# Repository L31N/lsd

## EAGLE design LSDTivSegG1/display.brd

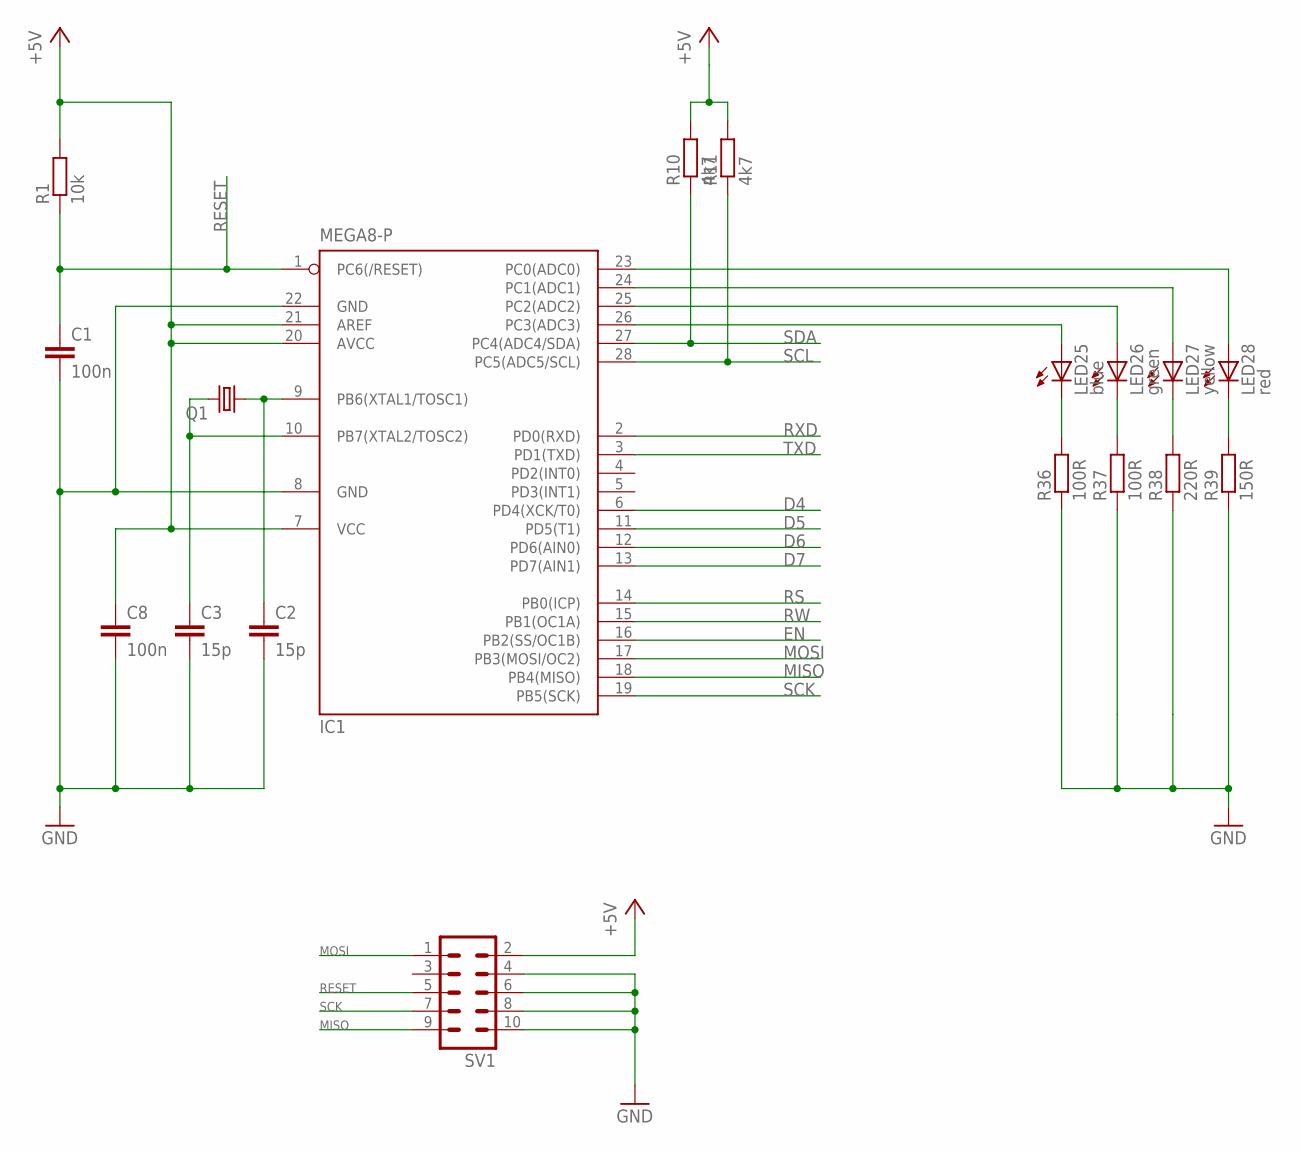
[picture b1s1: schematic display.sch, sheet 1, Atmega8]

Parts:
C1, C8: 100n; C025-025X050
C2, C3: 15p; C025-025X050
IC1: MEGA8-P; DIL28-3
LED25: blue; LED3MM
LED26: green; LED3MM
LED27: yellow; LED3MM
LED28: red; LED3MM
Q1: CRYSTALHC49U-V; HC49U-V
R1: 10k; 0207/10
R10, R11: 4k7; 0207/10
R36, R37: 100R; 0207/10
R38: 220R; 0207/10
R39: 150R; 0207/10
SV1: ML10

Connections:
+5V: C8.1, IC1.7 (VCC), IC1.20 (AVCC), IC1.21 (AREF), R1.2, R10.2, R11.2, SV1.2; also elsewhere on the board
D4: IC1.6 (PD4(XCK/T0)); also elsewhere on the board
D5: IC1.11 (PD5(T1)); also elsewhere on the board
D6: IC1.12 (PD6(AIN0)); also elsewhere on the board
D7: IC1.13 (PD7(AIN1)); also elsewhere on the board
EN: IC1.16 (PB2(SS/OC1B)); also elsewhere on the board
GND: C1.2, C2.2, C3.2, C8.2, IC1.8 (GND), IC1.22 (GND), R36.1, R37.1, R38.1, R39.1, SV1.4, SV1.6, SV1.8, SV1.10; also elsewhere on the board
MISO: IC1.18 (PB4(MISO)), SV1.9
MOSI: IC1.17 (PB3(MOSI/OC2)), SV1.1
unnamed: C2.1, IC1.9 (PB6(XTAL1/TOSC1)), Q1.1
unnamed: C3.1, IC1.10 (PB7(XTAL2/TOSC2)), Q1.2
unnamed: IC1.23 (PC0(ADC0)), LED28.A
unnamed: IC1.24 (PC1(ADC1)), LED27.A
unnamed: IC1.25 (PC2(ADC2)), LED26.A
unnamed: IC1.26 (PC3(ADC3)), LED25.A
unnamed: LED28.K (C), R39.2
unnamed: LED27.K (C), R38.2
unnamed: LED26.K (C), R37.2
unnamed: LED25.K (C), R36.2
RESET: C1.1, IC1.1 (PC6(/RESET)), R1.1, SV1.5
RS: IC1.14 (PB0(ICP)); also elsewhere on the board
RW: IC1.15 (PB1(OC1A)); also elsewhere on the board
RXD: IC1.2 (PD0(RXD)); also elsewhere on the board
SCK: IC1.19 (PB5(SCK)), SV1.7
SCL: IC1.28 (PC5(ADC5/SCL)), R11.1; also elsewhere on the board
SDA: IC1.27 (PC4(ADC4/SDA)), R10.1; also elsewhere on the board
TXD: IC1.3 (PD1(TXD)); also elsewhere on the board

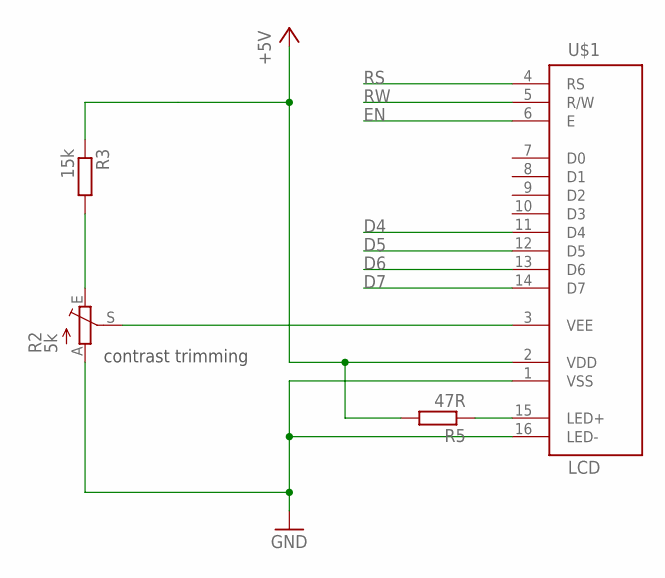
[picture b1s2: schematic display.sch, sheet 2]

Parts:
R2: 5k; PT-10
R3: 15k; 0207/10
R5: 47R; 0207/10
U$1: LCD

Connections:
+5V: R3.1, R5.2, U$1.2 (VDD); also elsewhere on the board
D4: U$1.11 (D4); also elsewhere on the board
D5: U$1.12 (D5); also elsewhere on the board
D6: U$1.13 (D6); also elsewhere on the board
D7: U$1.14 (D7); also elsewhere on the board
EN: U$1.6 (E); also elsewhere on the board
GND: R2.A, U$1.1 (VSS), U$1.16 (LED-); also elsewhere on the board
unnamed: R2.E, R3.2
unnamed: R2.S, U$1.3 (VEE)
unnamed: R5.1, U$1.15 (LED+)
RS: U$1.4 (RS); also elsewhere on the board
RW: U$1.5 (R/W); also elsewhere on the board

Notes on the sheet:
contrast trimming

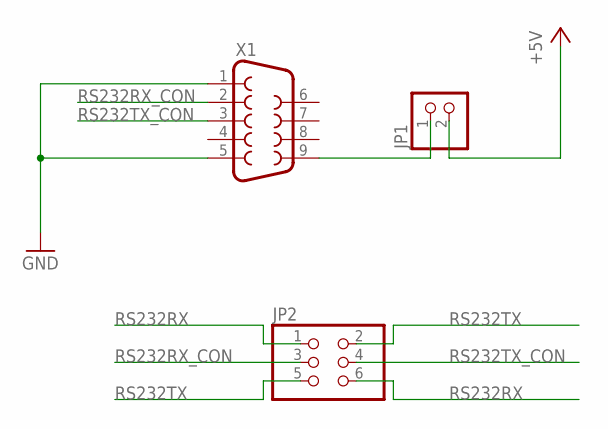
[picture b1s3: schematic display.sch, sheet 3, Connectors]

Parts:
JP1: PINHD-1X2; 1X02
JP2: PINHD-2X3; 2X03
X1: F09HP

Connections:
+5V: JP1.2; also elsewhere on the board
GND: X1.1, X1.5; also elsewhere on the board
unnamed: JP1.1, X1.9
RS232RX: JP2.1, JP2.6; also elsewhere on the board
RS232RX_CON: JP2.3, X1.2
RS232TX: JP2.2, JP2.5; also elsewhere on the board
RS232TX_CON: JP2.4, X1.3

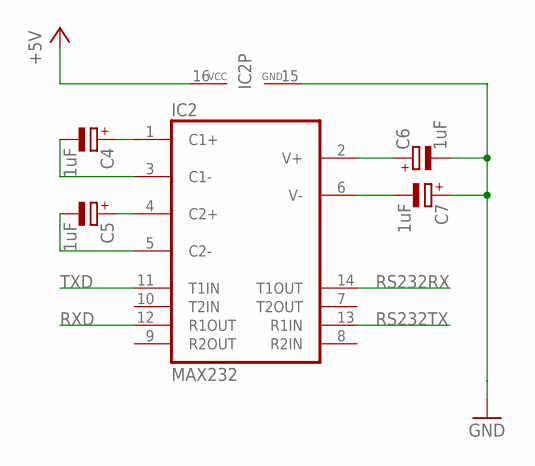
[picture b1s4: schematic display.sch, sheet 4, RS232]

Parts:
C4, C5, C6, C7: 1uF; E2,5-5
IC2: MAX232; DIL16

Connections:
+5V: IC2.16 (VCC); also elsewhere on the board
GND: C6.-, C7.+, IC2.15 (GND); also elsewhere on the board
unnamed: C4.+, IC2.1 (C1+)
unnamed: C5.+, IC2.4 (C2+)
unnamed: C5.-, IC2.5 (C2-)
unnamed: C4.-, IC2.3 (C1-)
unnamed: C6.+, IC2.2 (V+)
unnamed: C7.-, IC2.6 (V-)
RS232RX: IC2.14 (T1OUT); also elsewhere on the board
RS232TX: IC2.13 (R1IN); also elsewhere on the board
RXD: IC2.12 (R1OUT); also elsewhere on the board
TXD: IC2.11 (T1IN); also elsewhere on the board

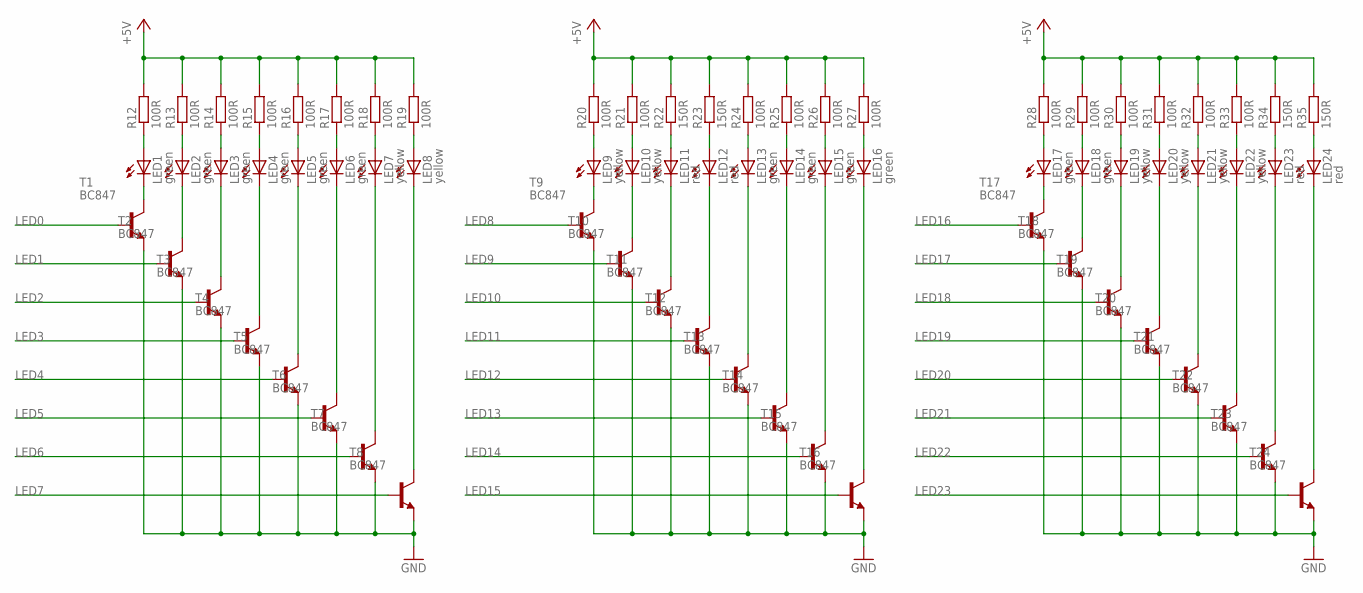
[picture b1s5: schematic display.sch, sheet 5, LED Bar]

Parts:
LED1, LED2, LED3, LED4, LED5, LED6, LED13, LED14, LED15, LED16, LED17, LED18: green; LED5MM
LED7, LED8, LED9, LED10, LED19, LED20, LED21, LED22: yellow; LED5MM
LED11, LED12, LED23, LED24: red; LED5MM
R12, R13, R14, R15, R16, R17, R18, R19, R20, R21, R24, R25, R26, R27, R28, R29, R30, R31, R32, R33: 100R; 0207/10
R22, R23, R34, R35: 150R; 0207/10
T1, T2, T3, T4, T5, T6, T7, T8, T9, T10, T11, T12, T13, T14, T15, T16, T17, T18, T19, T20, T21, T22, T23, T24: BC847; SOT23

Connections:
+5V: R12.2, R13.2, R14.2, R15.2, R16.2, R17.2, R18.2, R19.2, R20.2, R21.2, R22.2, R23.2, R24.2, R25.2, R26.2, R27.2, R28.2, R29.2, R30.2, R31.2, R32.2, R33.2, R34.2, R35.2; also elsewhere on the board
GND: T1.2 (E), T2.2 (E), T3.2 (E), T4.2 (E), T5.2 (E), T6.2 (E), T7.2 (E), T8.2 (E), T9.2 (E), T10.2 (E), T11.2 (E), T12.2 (E), T13.2 (E), T14.2 (E), T15.2 (E), T16.2 (E), T17.2 (E), T18.2 (E), T19.2 (E), T20.2 (E), T21.2 (E), T22.2 (E), T23.2 (E), T24.2 (E); also elsewhere on the board
LED0: T1.1 (B); also elsewhere on the board
LED1: T2.1 (B); also elsewhere on the board
LED2: T3.1 (B); also elsewhere on the board
LED3: T4.1 (B); also elsewhere on the board
LED4: T5.1 (B); also elsewhere on the board
LED5: T6.1 (B); also elsewhere on the board
LED6: T7.1 (B); also elsewhere on the board
LED7: T8.1 (B); also elsewhere on the board
LED8: T9.1 (B); also elsewhere on the board
LED9: T10.1 (B); also elsewhere on the board
LED10: T11.1 (B); also elsewhere on the board
LED11: T12.1 (B); also elsewhere on the board
LED12: T13.1 (B); also elsewhere on the board
LED13: T14.1 (B); also elsewhere on the board
LED14: T15.1 (B); also elsewhere on the board
LED15: T16.1 (B); also elsewhere on the board
LED16: T17.1 (B); also elsewhere on the board
LED17: T18.1 (B); also elsewhere on the board
LED18: T19.1 (B); also elsewhere on the board
LED19: T20.1 (B); also elsewhere on the board
LED20: T21.1 (B); also elsewhere on the board
LED21: T22.1 (B); also elsewhere on the board
LED22: T23.1 (B); also elsewhere on the board
LED23: T24.1 (B); also elsewhere on the board
unnamed: LED1.A, R12.1
unnamed: LED2.A, R13.1
unnamed: LED3.A, R14.1
unnamed: LED4.A, R15.1
unnamed: LED5.A, R16.1
unnamed: LED6.A, R17.1
unnamed: LED7.A, R18.1
unnamed: LED8.A, R19.1
unnamed: LED9.A, R20.1
unnamed: LED10.A, R21.1
unnamed: LED11.A, R22.1
unnamed: LED12.A, R23.1
unnamed: LED13.A, R24.1
unnamed: LED14.A, R25.1
unnamed: LED15.A, R26.1
unnamed: LED16.A, R27.1
unnamed: LED17.A, R28.1
unnamed: LED18.A, R29.1
unnamed: LED19.A, R30.1
unnamed: LED20.A, R31.1
unnamed: LED21.A, R32.1
unnamed: LED22.A, R33.1
unnamed: LED23.A, R34.1
unnamed: LED24.A, R35.1
unnamed: LED9.K (C), T9.3 (C)
unnamed: LED1.K (C), T1.3 (C)
unnamed: LED2.K (C), T2.3 (C)
unnamed: LED3.K (C), T3.3 (C)
unnamed: LED4.K (C), T4.3 (C)
unnamed: LED5.K (C), T5.3 (C)
unnamed: LED6.K (C), T6.3 (C)
unnamed: LED17.K (C), T17.3 (C)
unnamed: LED10.K (C), T10.3 (C)
unnamed: LED11.K (C), T11.3 (C)
unnamed: LED12.K (C), T12.3 (C)
unnamed: LED13.K (C), T13.3 (C)
unnamed: LED14.K (C), T14.3 (C)
unnamed: LED7.K (C), T7.3 (C)
unnamed: LED8.K (C), T8.3 (C)
unnamed: LED15.K (C), T15.3 (C)
unnamed: LED16.K (C), T16.3 (C)
unnamed: LED18.K (C), T18.3 (C)
unnamed: LED19.K (C), T19.3 (C)
unnamed: LED20.K (C), T20.3 (C)
unnamed: LED21.K (C), T21.3 (C)
unnamed: LED22.K (C), T22.3 (C)
unnamed: LED23.K (C), T23.3 (C)
unnamed: LED24.K (C), T24.3 (C)

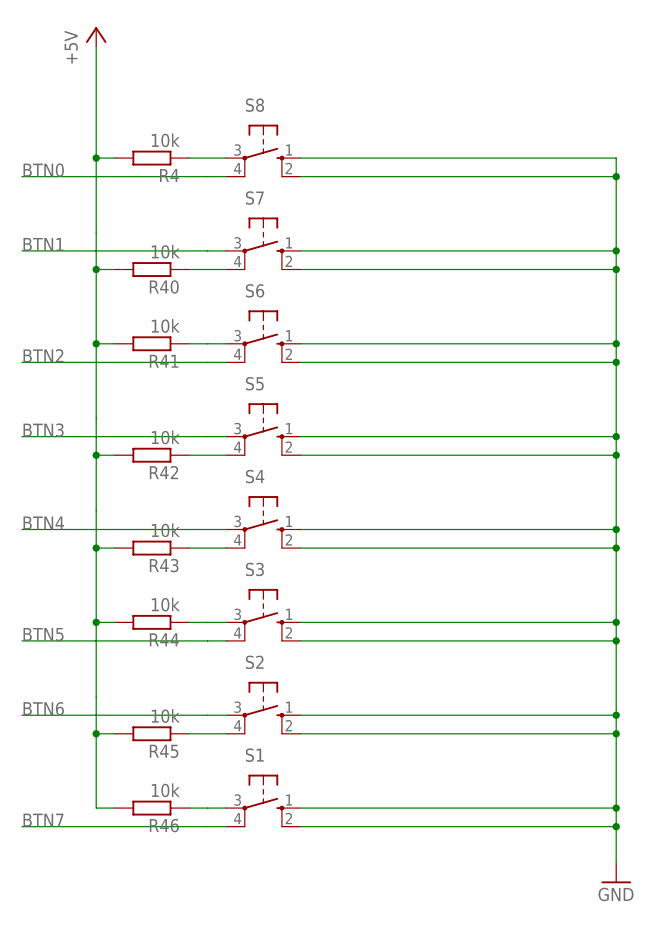
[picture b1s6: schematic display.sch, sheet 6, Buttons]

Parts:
R4, R40, R41, R42, R43, R44, R45, R46: 10k; R0805
S1, S2, S3, S4, S5, S6, S7, S8: 10-XX; B3F-10XX

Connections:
+5V: R4.2, R40.2, R41.2, R42.2, R43.2, R44.2, R45.2, R46.2; also elsewhere on the board
BTN0: S8.4 (P1); also elsewhere on the board
BTN1: S7.3; also elsewhere on the board
BTN2: S6.4 (P1); also elsewhere on the board
BTN3: S5.3; also elsewhere on the board
BTN4: S4.3; also elsewhere on the board
BTN5: S3.4 (P1); also elsewhere on the board
BTN6: S2.3; also elsewhere on the board
BTN7: S1.4 (P1); also elsewhere on the board
GND: S1.1 (S), S1.2 (S1), S2.1 (S), S2.2 (S1), S3.1 (S), S3.2 (S1), S4.1 (S), S4.2 (S1), S5.1 (S), S5.2 (S1), S6.1 (S), S6.2 (S1), S7.1 (S), S7.2 (S1), S8.1 (S), S8.2 (S1); also elsewhere on the board
unnamed: R4.1, S8.3
unnamed: R41.1, S6.3
unnamed: R45.1, S2.4 (P1)
unnamed: R43.1, S4.4 (P1)
unnamed: R44.1, S3.3
unnamed: R42.1, S5.4 (P1)
unnamed: R46.1, S1.3
unnamed: R40.1, S7.4 (P1)

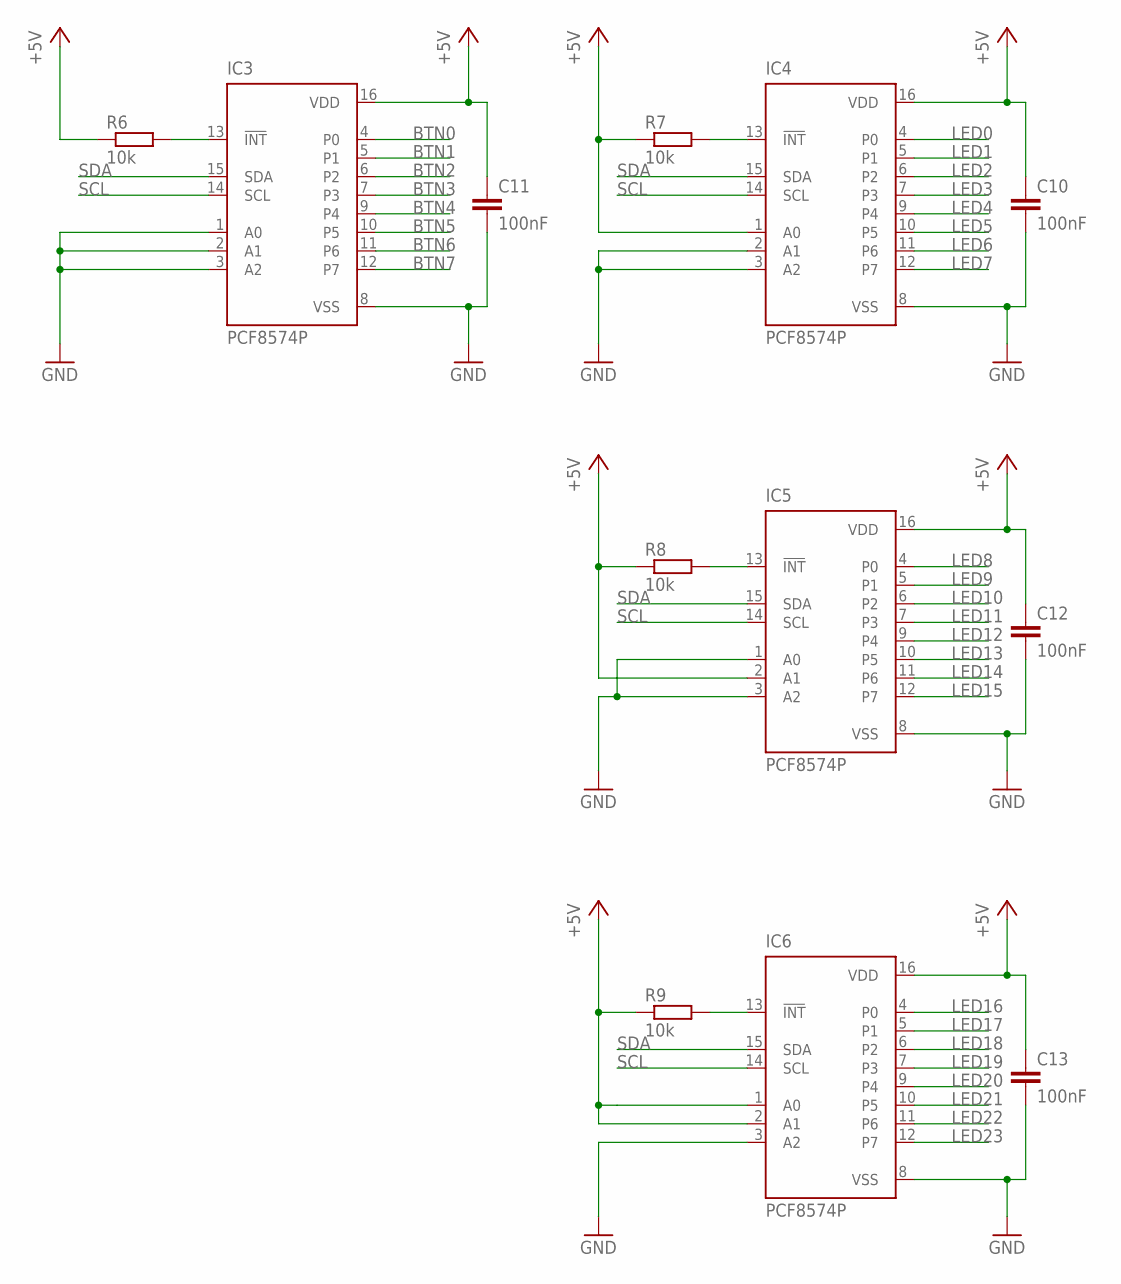
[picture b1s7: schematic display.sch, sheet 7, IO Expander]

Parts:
C10, C11, C12, C13: 100nF; C025-025X050
IC3, IC4, IC5, IC6: PCF8574P; DIL16
R6, R7, R8, R9: 10k; 0207/10

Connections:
+5V: C10.1, C11.1, C12.1, C13.1, IC3.16 (VDD), IC4.1 (A0), IC4.16 (VDD), IC5.2 (A1), IC5.16 (VDD), IC6.1 (A0), IC6.2 (A1), IC6.16 (VDD), R6.1, R7.1, R8.1, R9.1; also elsewhere on the board
BTN0: IC3.4 (P0); also elsewhere on the board
BTN1: IC3.5 (P1); also elsewhere on the board
BTN2: IC3.6 (P2); also elsewhere on the board
BTN3: IC3.7 (P3); also elsewhere on the board
BTN4: IC3.9 (P4); also elsewhere on the board
BTN5: IC3.10 (P5); also elsewhere on the board
BTN6: IC3.11 (P6); also elsewhere on the board
BTN7: IC3.12 (P7); also elsewhere on the board
GND: C10.2, C11.2, C12.2, C13.2, IC3.1 (A0), IC3.2 (A1), IC3.3 (A2), IC3.8 (VSS), IC4.2 (A1), IC4.3 (A2), IC4.8 (VSS), IC5.1 (A0), IC5.3 (A2), IC5.8 (VSS), IC6.3 (A2), IC6.8 (VSS); also elsewhere on the board
LED0: IC4.4 (P0); also elsewhere on the board
LED1: IC4.5 (P1); also elsewhere on the board
LED2: IC4.6 (P2); also elsewhere on the board
LED3: IC4.7 (P3); also elsewhere on the board
LED4: IC4.9 (P4); also elsewhere on the board
LED5: IC4.10 (P5); also elsewhere on the board
LED6: IC4.11 (P6); also elsewhere on the board
LED7: IC4.12 (P7); also elsewhere on the board
LED8: IC5.4 (P0); also elsewhere on the board
LED9: IC5.5 (P1); also elsewhere on the board
LED10: IC5.6 (P2); also elsewhere on the board
LED11: IC5.7 (P3); also elsewhere on the board
LED12: IC5.9 (P4); also elsewhere on the board
LED13: IC5.10 (P5); also elsewhere on the board
LED14: IC5.11 (P6); also elsewhere on the board
LED15: IC5.12 (P7); also elsewhere on the board
LED16: IC6.4 (P0); also elsewhere on the board
LED17: IC6.5 (P1); also elsewhere on the board
LED18: IC6.6 (P2); also elsewhere on the board
LED19: IC6.7 (P3); also elsewhere on the board
LED20: IC6.9 (P4); also elsewhere on the board
LED21: IC6.10 (P5); also elsewhere on the board
LED22: IC6.11 (P6); also elsewhere on the board
LED23: IC6.12 (P7); also elsewhere on the board
unnamed: IC3.13 (!INT), R6.2
unnamed: IC4.13 (!INT), R7.2
unnamed: IC5.13 (!INT), R8.2
unnamed: IC6.13 (!INT), R9.2
SCL: IC3.14 (SCL), IC4.14 (SCL), IC5.14 (SCL), IC6.14 (SCL); also elsewhere on the board
SDA: IC3.15 (SDA), IC4.15 (SDA), IC5.15 (SDA), IC6.15 (SDA); also elsewhere on the board

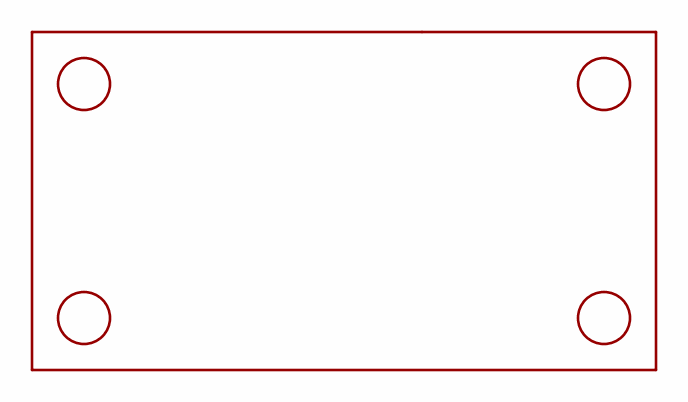
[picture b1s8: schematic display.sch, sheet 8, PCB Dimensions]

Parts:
U$2: DISPLAY_FRAME

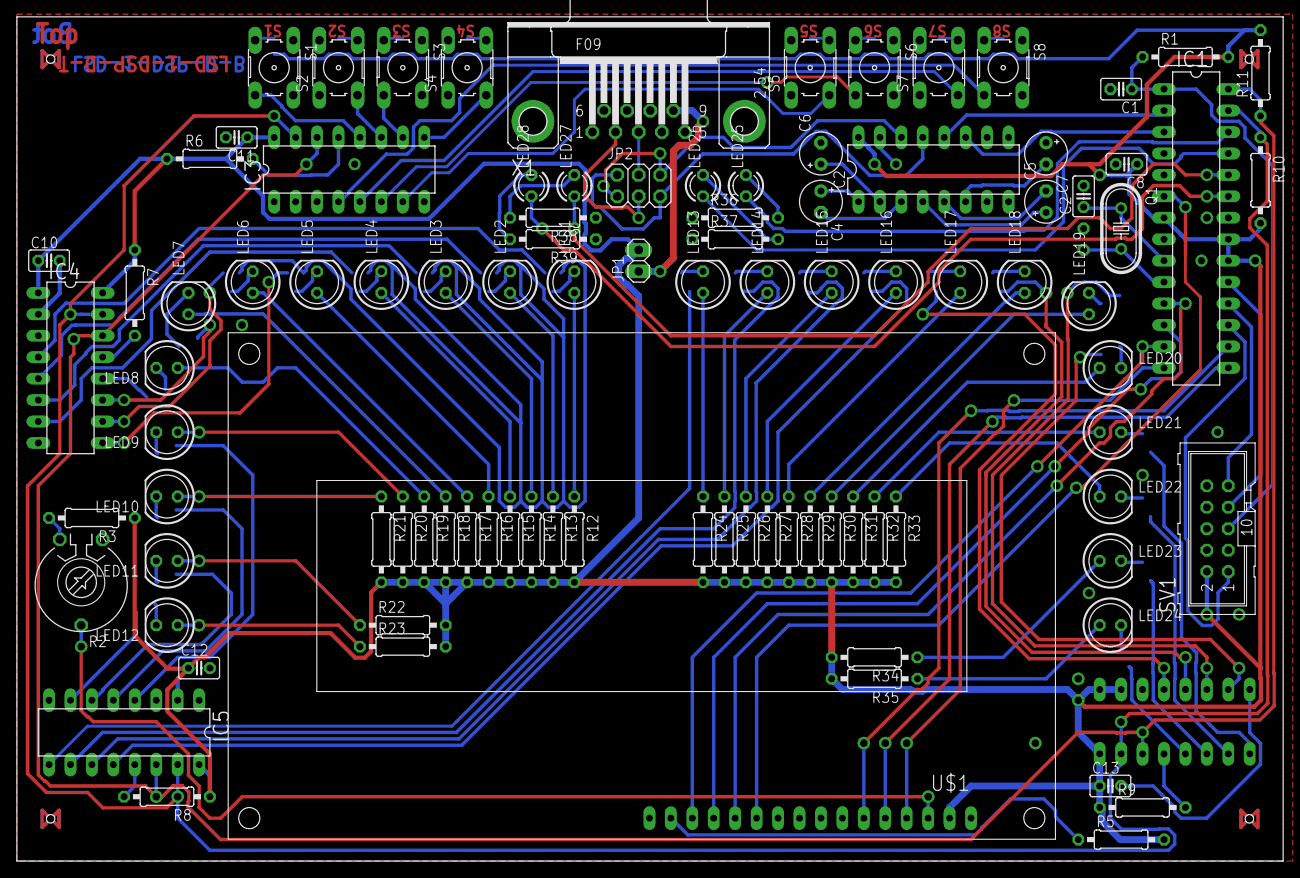
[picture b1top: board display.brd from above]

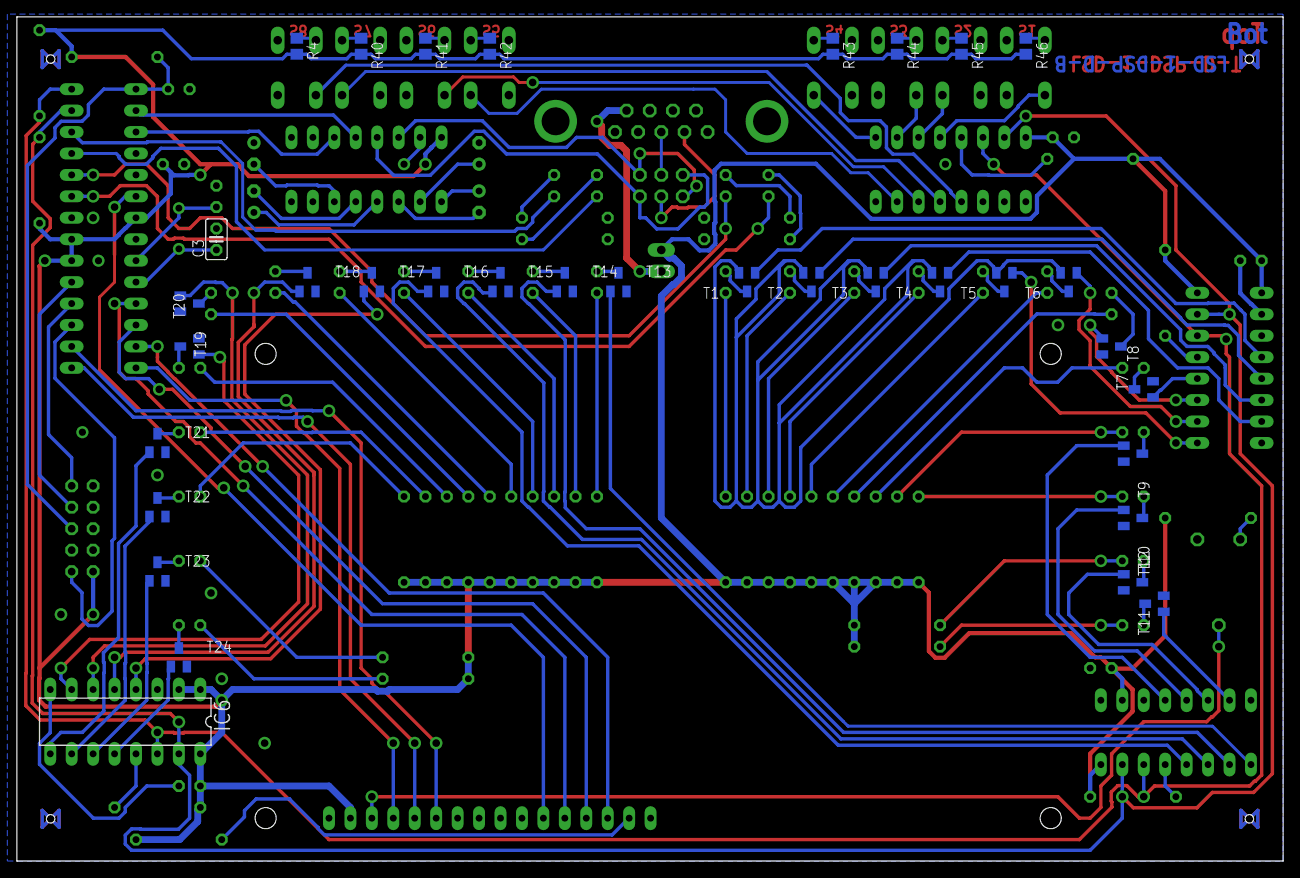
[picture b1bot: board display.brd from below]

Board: 2 copper layers, 150.0 x 100.0 mm, 131 parts (34 on the bottom side), 133 nets.

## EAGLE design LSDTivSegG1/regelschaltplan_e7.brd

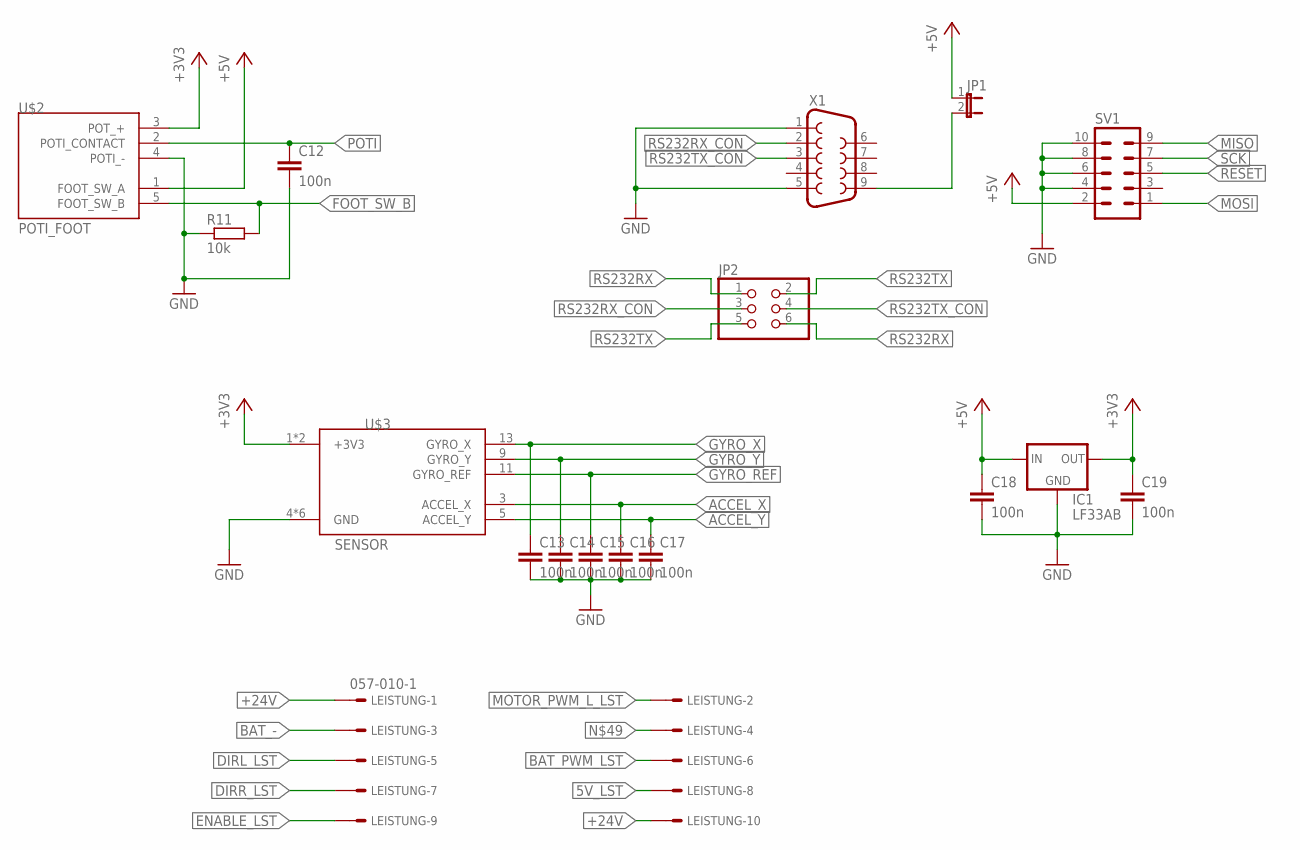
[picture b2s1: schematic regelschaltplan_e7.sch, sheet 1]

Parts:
C12, C13, C14, C15, C16, C17, C18, C19: 100n; C025-025X050
IC1: LF33AB; TO220
JP1: JP1E; JP1
JP2: PINHD-2X3; 2X03
LEISTUNG: 057-010-1
R11: 10k; 0207/7
SV1: MA05-2
U$2: POTI_FOOT; CON_6
U$3: SENSOR; CON_14
X1: F09HP

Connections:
5V_LST: LEISTUNG.8; also elsewhere on the board
+3V3: C19.1, IC1.3 (OUT), U$2.3 (POT_+), U$3.1 (+3V3), U$3.2 (+3V3); also elsewhere on the board
+24V: LEISTUNG.1, LEISTUNG.10; also elsewhere on the board
ACCEL_X: C16.1, U$3.3 (ACCEL_X); also elsewhere on the board
ACCEL_Y: C17.1, U$3.5 (ACCEL_Y); also elsewhere on the board
BAT_-: LEISTUNG.3; also elsewhere on the board
BAT_PWM_LST: LEISTUNG.6; also elsewhere on the board
DIRL_LST: LEISTUNG.5; also elsewhere on the board
DIRR_LST: LEISTUNG.7; also elsewhere on the board
ENABLE_LST: LEISTUNG.9; also elsewhere on the board
FOOT_SW_B: R11.2, U$2.5 (FOOT_SW_B); also elsewhere on the board
GND: C12.2, C13.2, C14.2, C15.2, C16.2, C17.2, C18.2, C19.2, IC1.2 (GND), R11.1, SV1.4, SV1.6, SV1.8, SV1.10, U$2.4 (POTI_-), U$3.4 (GND), U$3.6 (GND), U$3.8 (GND), U$3.10 (GND), U$3.12 (GND), U$3.14 (GND), X1.1, X1.5; also elsewhere on the board
GYRO_REF: C15.1, U$3.11 (GYRO_REF); also elsewhere on the board
GYRO_X: C13.1, U$3.13 (GYRO_X); also elsewhere on the board
GYRO_Y: C14.1, U$3.9 (GYRO_Y); also elsewhere on the board
MISO: SV1.9; also elsewhere on the board
MOSI: SV1.1; also elsewhere on the board
MOTOR_PWM_L_LST: LEISTUNG.2; also elsewhere on the board
unnamed 58: C18.1, IC1.1 (IN), JP1.1, SV1.2, U$2.1 (FOOT_SW_A); also elsewhere on the board
unnamed: JP1.2, X1.9
unnamed 71: LEISTUNG.4; also elsewhere on the board
POTI: C12.1, U$2.2 (POTI_CONTACT); also elsewhere on the board
RESET: SV1.5; also elsewhere on the board
RS232RX: JP2.1, JP2.6; also elsewhere on the board
RS232RX_CON: JP2.3, X1.2
RS232TX: JP2.2, JP2.5; also elsewhere on the board
RS232TX_CON: JP2.4, X1.3
SCK: SV1.7; also elsewhere on the board

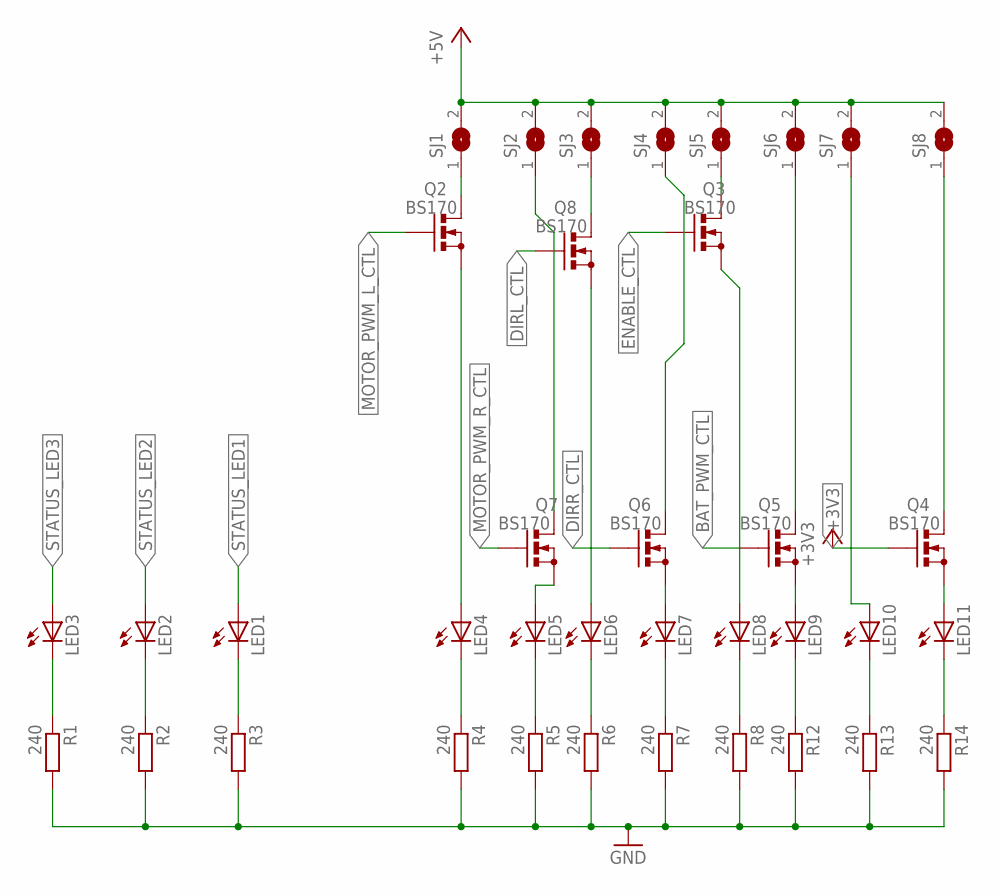
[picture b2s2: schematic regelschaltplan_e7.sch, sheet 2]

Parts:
LED1, LED2, LED3, LED4, LED5, LED6, LED7, LED8, LED9, LED10, LED11: LED3MM
Q2, Q3, Q4, Q5, Q6, Q7, Q8: BS170; SOT54E
R1, R2, R3, R4, R5, R6, R7, R8, R12, R13, R14: 240; 0207/7
SJ1, SJ2, SJ3, SJ4, SJ5, SJ6, SJ7, SJ8: SJ

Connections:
+3V3: Q4.G; also elsewhere on the board
BAT_PWM_CTL: Q5.G; also elsewhere on the board
DIRL_CTL: Q8.G; also elsewhere on the board
DIRR_CTL: Q6.G; also elsewhere on the board
ENABLE_CTL: Q3.G; also elsewhere on the board
GND: R1.2, R2.2, R3.2, R4.2, R5.2, R6.2, R7.2, R8.2, R12.2, R13.2, R14.2; also elsewhere on the board
MOTOR_PWM_L_CTL: Q2.G; also elsewhere on the board
MOTOR_PWM_R_CTL: Q7.G; also elsewhere on the board
unnamed: Q2.D, SJ1.1
unnamed: LED4.K (C), R4.1
unnamed: LED5.K (C), R5.1
unnamed: LED6.K (C), R6.1
unnamed: LED6.A, Q8.S
unnamed: LED7.K (C), R7.1
unnamed: LED8.K (C), R8.1
unnamed: LED9.K (C), R12.1
unnamed: LED10.K (C), R13.1
unnamed: LED11.K (C), R14.1
unnamed: LED8.A, Q3.S
unnamed: LED10.A, SJ7.1
unnamed: LED9.A, Q5.S
unnamed: Q4.D, SJ8.1
unnamed: LED7.A, Q6.S
unnamed: LED5.A, Q7.S
unnamed: Q7.D, SJ2.1
unnamed: LED4.A, Q2.S
unnamed: LED11.A, Q4.S
unnamed: LED2.K (C), R2.1
unnamed: LED3.K (C), R1.1
unnamed: Q6.D, SJ4.1
unnamed: Q5.D, SJ6.1
unnamed: Q3.D, SJ5.1
unnamed: Q8.D, SJ3.1
unnamed 58: SJ1.2, SJ2.2, SJ3.2, SJ4.2, SJ5.2, SJ6.2, SJ7.2, SJ8.2; also elsewhere on the board
unnamed: LED1.K (C), R3.1
STATUS_LED1: LED1.A; also elsewhere on the board
STATUS_LED2: LED2.A; also elsewhere on the board
STATUS_LED3: LED3.A; also elsewhere on the board

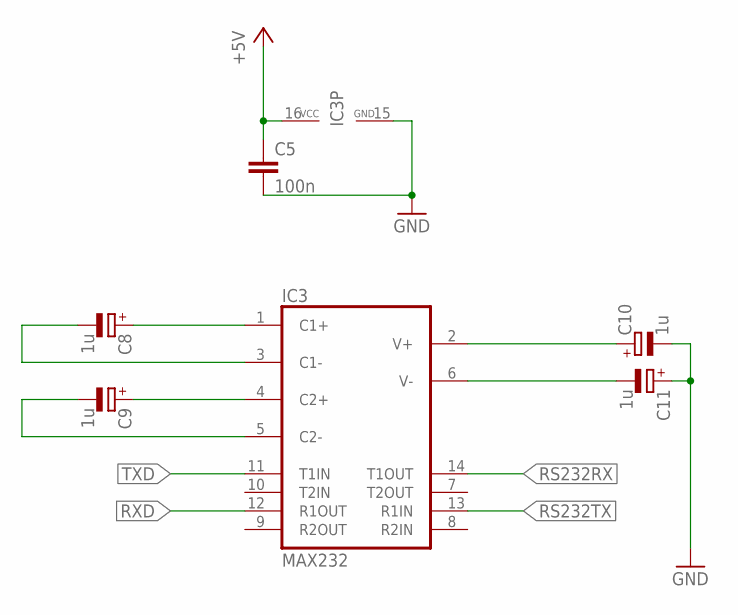
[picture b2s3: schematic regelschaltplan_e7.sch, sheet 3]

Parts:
C5: 100n; C025-025X050
C8, C9, C10, C11: 1u; E2,5-6E
IC3: MAX232; DIL16

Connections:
GND: C5.2, C10.-, C11.+, IC3.15 (GND); also elsewhere on the board
unnamed: C8.+, IC3.1 (C1+)
unnamed: C8.-, IC3.3 (C1-)
unnamed: C9.+, IC3.4 (C2+)
unnamed: C10.+, IC3.2 (V+)
unnamed: C11.-, IC3.6 (V-)
unnamed 58: C5.1, IC3.16 (VCC); also elsewhere on the board
NS1234: C9.-, IC3.5 (C2-)
RS232RX: IC3.14 (T1OUT); also elsewhere on the board
RS232TX: IC3.13 (R1IN); also elsewhere on the board
RXD: IC3.12 (R1OUT); also elsewhere on the board
TXD: IC3.11 (T1IN); also elsewhere on the board

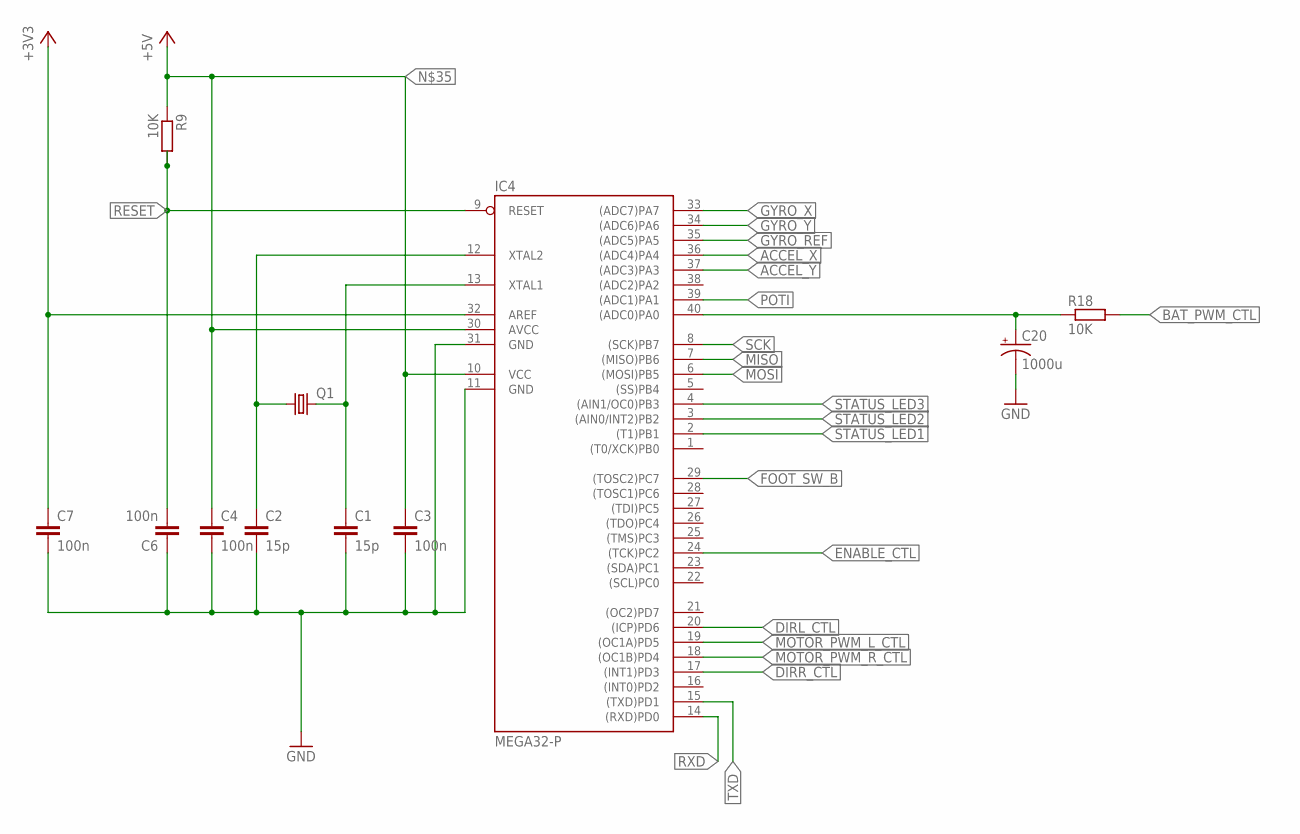
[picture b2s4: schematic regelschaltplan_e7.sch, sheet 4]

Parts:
C1, C2: 15p; C025-025X050
C3, C4, C6, C7: 100n; C025-025X050
C20: 1000u; E2,5-6E
IC4: MEGA32-P; DIL40
Q1: CRYSTALHC49U-V; HC49U-V
R9, R18: 10K; 0207/7

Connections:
+3V3: C7.1, IC4.32 (AREF); also elsewhere on the board
ACCEL_X: IC4.36 ((ADC4)PA4); also elsewhere on the board
ACCEL_Y: IC4.37 ((ADC3)PA3); also elsewhere on the board
BAT_PWM_CTL: R18.2; also elsewhere on the board
DIRL_CTL: IC4.20 ((ICP)PD6); also elsewhere on the board
DIRR_CTL: IC4.17 ((INT1)PD3); also elsewhere on the board
ENABLE_CTL: IC4.24 ((TCK)PC2); also elsewhere on the board
FOOT_SW_B: IC4.29 ((TOSC2)PC7); also elsewhere on the board
GND: C1.2, C2.2, C3.2, C4.2, C6.1, C7.2, C20.-, IC4.11 (GND), IC4.31 (GND); also elsewhere on the board
GYRO_REF: IC4.35 ((ADC5)PA5); also elsewhere on the board
GYRO_X: IC4.33 ((ADC7)PA7); also elsewhere on the board
GYRO_Y: IC4.34 ((ADC6)PA6); also elsewhere on the board
MISO: IC4.7 ((MISO)PB6); also elsewhere on the board
MOSI: IC4.6 ((MOSI)PB5); also elsewhere on the board
MOTOR_PWM_L_CTL: IC4.19 ((OC1A)PD5); also elsewhere on the board
MOTOR_PWM_R_CTL: IC4.18 ((OC1B)PD4); also elsewhere on the board
unnamed: C2.1, IC4.12 (XTAL2), Q1.1
unnamed: C1.1, IC4.13 (XTAL1), Q1.2
unnamed: C20.+, IC4.40 ((ADC0)PA0), R18.1
unnamed 58: C3.1, C4.1, IC4.10 (VCC), IC4.30 (AVCC), R9.1; also elsewhere on the board
POTI: IC4.39 ((ADC1)PA1); also elsewhere on the board
RESET: C6.2, IC4.9 (RESET), R9.2; also elsewhere on the board
RXD: IC4.14 ((RXD)PD0); also elsewhere on the board
SCK: IC4.8 ((SCK)PB7); also elsewhere on the board
STATUS_LED1: IC4.2 ((T1)PB1); also elsewhere on the board
STATUS_LED2: IC4.3 ((AIN0/INT2)PB2); also elsewhere on the board
STATUS_LED3: IC4.4 ((AIN1/OC0)PB3); also elsewhere on the board
TXD: IC4.15 ((TXD)PD1); also elsewhere on the board

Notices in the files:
parts and their libraries:
SparkFun-Aesthetics: Licensing: CC v3.0 Share-Alike You are welcome to use this library for commercial purposes.
